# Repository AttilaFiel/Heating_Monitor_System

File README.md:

# HMS – Fűtésfelügyeleti rendszer

### HMS_Master
A rendszer központi egysége, amely a kazánházban található érzékelők adatait gyűjti és feldolgozza. Figyeli a fűtési rendszer hőmérsékleteit, a kazánok működését és a különböző hibajelzéseket. Az adatokat kijelzi, naplózza, valamint Wi-Fi-n keresztül elérhetővé teszi a többi eszköz és a központi felügyeleti rendszer számára. Vizuális és hangjelzésekkel figyelmeztet a rendellenes működésre.

### HMS_Display
A HMS_Master és a HMS_Kids_Thermometer adatait megjelenítő, önállóan működő kijelzőegység, amely a lakótérben helyezhető el. Érintőképernyőjén megjeleníti a fűtési rendszer aktuális állapotát, a hőmérsékleteket, a páratartalmat és a riasztásokat. Hang- és fényjelzésekkel figyelmeztet a fontosabb eseményekre. Wi-Fi-n keresztül kommunikál a többi eszközzel.

### HMS_Kids_Thermometer
Önálló, Wi-Fi-kapcsolattal rendelkező szobai hőmérséklet- és páratartalom-mérő eszköz. Az SHT30 érzékelő segítségével méri a környezeti hőmérsékletet és páratartalmat. A mért adatokat hálózaton keresztül elérhetővé teszi, így a szoba klímája távolról is ellenőrizhető. Elsősorban a gyerekszoba környezeti viszonyainak folyamatos megfigyelésére szolgál.

</br>

# HMS hardverlista

## HMS_Master

### Hardver:
- ESP32 DevKitC-32UE mikrokontroller
- 2× SSD1306 SPI OLED kijelzőmodul
- DS3231 RTC + AT24C32 EEPROM valós idejű óramodul
- MAX6675 K-típusú hőmérséklet-érzékelő modul
- 5× DS18B20 digitális hőmérséklet-érzékelő
- DHT11 hőmérséklet- és páratartalom-érzékelő
- microSD SPI memóriakártya-modul
- 2× MVPDM-1PHS váltakozó feszültség érzékelőmodul
- 3× közös katódos RGB LED
- Aktív hangjelző (buzzer)

### Tápellátás:
- 5 V-os tápbemenet
- Beépített 3,3 V-os feszültségszabályozó

---

## HMS_Display

### Hardver:
- ESP32 DevKitC-32UE mikrokontroller
- MSP2807 2,8"-os TFT SPI érintőképernyő-modul (ILI9341 + XPT2046)
- DS3231 RTC + AT24C32 EEPROM valós idejű óramodul
- SHT30-M hőmérséklet- és páratartalom-érzékelő
- Fényérzékelő (fotóellenállás)
- Közös katódos RGB LED
- 2× aktív hangjelző (buzzer)

### Tápellátás:
- 5 V-os USB-tápbemenet
- Beépített 3,3 V-os feszültségszabályozó

---

## HMS_Kids_Thermometer

### Hardver:
- ESP32-C3-SUPERMINI mikrokontroller
- SHT30 hőmérséklet- és páratartalom-érzékelő

### Tápellátás:
- 5 V-os tápbemenet
- Beépített 3,3 V-os feszültségszabályozó

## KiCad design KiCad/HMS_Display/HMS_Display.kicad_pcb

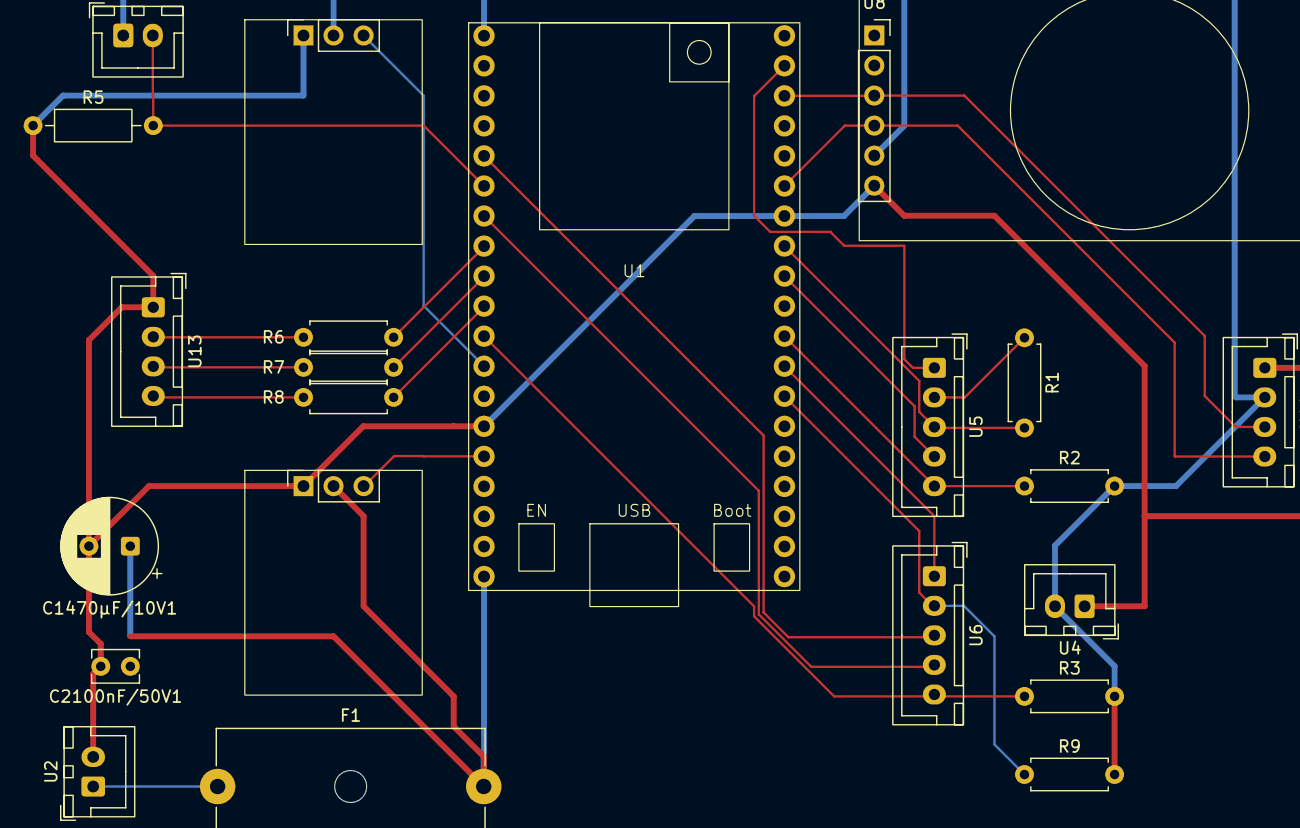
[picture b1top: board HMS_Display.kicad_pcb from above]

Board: 2 copper layers, 22 parts (0 on the bottom side), 25 nets.

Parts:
C1470µF/10V1: 470µF 10V; CP_Radial_D8.0mm_P3.50mm
C2100nF/50V1: 100nF 50V; C_Disc_D3.8mm_W2.6mm_P2.50mm
F1: T1A Fuse; Fuseholder_Cylinder-5x20mm_Schurter_0031_8201_Horizontal_Op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
R1: DNP SOCKET; R_Axial_DIN0207_L6.3mm_D2.5mm_P7.62mm_Horizontal
R2, R3, R9: SOCKET; R_Axial_DIN0207_L6.3mm_D2.5mm_P7.62mm_Horizontal
R5: 10kΩ; R_Axial_DIN0207_L6.3mm_D2.5mm_P10.16mm_Horizontal
R6, R7, R8: 220Ω; R_Axial_DIN0207_L6.3mm_D2.5mm_P7.62mm_Horizontal
U1: ESP32-DEVKITC-32UE; ESP32_DEVKITC_32UE
U2: USB-C_POWER_CONNECTOR; JST_XH_B2B-XH-A_1x02_P2.50mm_Vertical
U4: DISPLAY_POWER_CONNECTOR; JST_XH_B2B-XH-A_1x02_P2.50mm_Vertical
U5: DISPLAY_DATA_CONNECTOR_1; JST_XH_B5B-XH-A_1x05_P2.50mm_Vertical
U6: DISPLAY_DATA_CONNECTOR_2; JST_XH_B5B-XH-A_1x05_P2.50mm_Vertical
U8: DS3231+AT24C32; PinSocket_1x06_P2.54mm_Vertical
U9, U10: KY-012
U11: SHT30_CONNECTOR; JST_XH_B4B-XH-A_1x04_P2.50mm_Vertical
U12: PHOTORESISTOR_CONNECTOR; JST_XH_B2B-XH-A_1x02_P2.50mm_Vertical
U13: LED_CONNECTOR; JST_XH_B4B-XH-A_1x04_P2.50mm_Vertical

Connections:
/01_ESP32/BUZZER_1: U1.12 (GPIO14), U9.3 (SIGNAL)
/01_ESP32/BUZZER_2: U1.15 (GPIO13), U10.3 (SIGNAL)
/01_ESP32/DISPLAY_CS: R2.1, U1.30 (GPIO17), U5.5
/01_ESP32/DISPLAY_DC: U1.31 (GPIO16), U6.1
/01_ESP32/DISPLAY_LED: U1.7 (GPIO32), U6.4
/01_ESP32/DISPLAY_RESET: R9.1, U1.32 (GPIO4), U6.2
/01_ESP32/I2C_SCL: U1.22 (GPIO22), U8.3 (SCL), U11.3
/01_ESP32/I2C_SDA: U1.25 (GPIO21), U8.4 (SDA), U11.4
/01_ESP32/LED_B: R8.1, U1.10 (GPIO26)
/01_ESP32/LED_G: R7.1, U1.9 (GPIO25)
/01_ESP32/LED_R: R6.1, U1.8 (GPIO33)
/01_ESP32/PHOTORESISTOR: R5.2, U1.6 (GPIO35), U12.2
/01_ESP32/PWR_3V3_OUT: R2.2, R3.2, R9.2, U1.1 (3V3), U4.2, U8.5 (VCC), U9.2 (VCC), U11.2, U12.1
/01_ESP32/PWR_5V_IN: C1470µF/10V1.1, C2100nF/50V1.1, F1.2, U1.19 (5V), U10.2 (VCC)
/01_ESP32/PWR_GND: C1470µF/10V1.2, C2100nF/50V1.2, R5.1, U1.14 (GND), U1.20 (GND), U1.26 (GND), U2.2, U4.1, U8.6 (GND), U9.1 (GRN), U10.1 (GRN), U11.1, U13.1
/01_ESP32/SPI_MISO: R1.2, U1.27 (GPIO19), U5.3
/01_ESP32/SPI_MOSI: U1.21 (GPIO23), U5.1
/01_ESP32/SPI_SCK: U1.28 (GPIO18), U5.4
/01_ESP32/T_CS: R3.1, U1.11 (GPIO27), U6.5
/01_ESP32/T_IRQ: U1.5 (GPIO34), U6.3
unnamed: F1.1, U2.1
unnamed: R1.1, U5.2
unnamed: R6.2, U13.2
unnamed: R7.2, U13.3
unnamed: R8.2, U13.4

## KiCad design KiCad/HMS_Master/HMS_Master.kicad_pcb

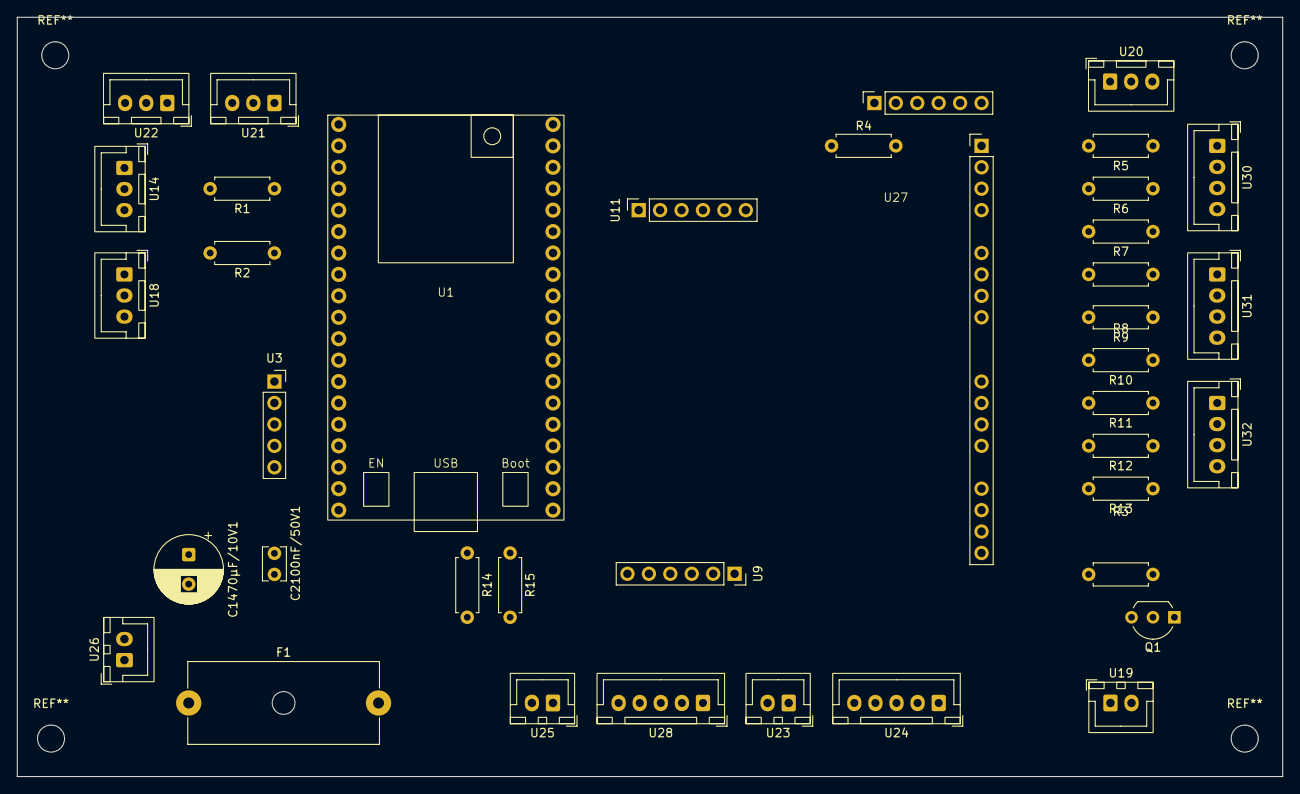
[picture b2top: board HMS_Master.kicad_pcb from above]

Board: 2 copper layers, 150.0 x 90.0 mm, 38 parts (0 on the bottom side), 44 nets.

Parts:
C1470µF/10V1: 470µF 10V; CP_Radial_D8.0mm_P3.50mm
C2100nF/50V1: 100nF 50V; C_Disc_D3.8mm_W2.6mm_P2.50mm
F1: T1A Fuse; Fuseholder_Cylinder-5x20mm_Schurter_0031_8201_Horizontal_Op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
Q1: S8050; TO-92_Inline_Wide
R1: 4,7kΩ; R_Axial_DIN0207_L6.3mm_D2.5mm_P7.62mm_Horizontal
R2: 33Ω; R_Axial_DIN0207_L6.3mm_D2.5mm_P7.62mm_Horizontal
R3: 1kΩ; R_Axial_DIN0207_L6.3mm_D2.5mm_P7.62mm_Horizontal
R4: 10kΩ; R_Axial_DIN0207_L6.3mm_D2.5mm_P7.62mm_Horizontal
R5, R6, R7, R8, R9, R10, R11, R12, R13: 220Ω; R_Axial_DIN0207_L6.3mm_D2.5mm_P7.62mm_Horizontal
R14, R15: 100Ω; R_Axial_DIN0207_L6.3mm_D2.5mm_P7.62mm_Horizontal
U1: ESP32-DEVKITC-32UE; ESP32_DEVKITC_32UE
U3: MAX6675; PinSocket_1x05_P2.54mm_Vertical
U9: DS3231+AT24C32; PinSocket_1x06_P2.54mm_Vertical
U11: MICROSD_SPI_3V3; PinSocket_1x06_P2.54mm_Vertical
U14: PIPE_SENSORS_SOCKET; JST_XH_B3B-XH-A_1x03_P2.50mm_Vertical
U18: WOOD_BOILER_SENSOR_SOCKET; JST_XH_B3B-XH-A_1x03_P2.50mm_Vertical
U19: BUZZER_SOCKET; JST_XH_B2B-XH-A_1x02_P2.50mm_Vertical
U20: BOILER_ROOM_SENSOR_SOCKET; JST_XH_B3B-XH-A_1x03_P2.50mm_Vertical
U21: GAS_AC_PRESENT_SOCKET; JST_XH_B3B-XH-A_1x03_P2.50mm_Vertical
U22: WOOD_AC_PRESENT_SOCKET; JST_XH_B3B-XH-A_1x03_P2.50mm_Vertical
U23: DISPLAY1_POWER_SOCKET; JST_XH_B2B-XH-A_1x02_P2.50mm_Vertical
U24: DISPLAY1_DATA_SOCKET; JST_XH_B5B-XH-A_1x05_P2.50mm_Vertical
U25: DISPLAY2_POWER_SOCKET; JST_XH_B2B-XH-A_1x02_P2.50mm_Vertical
U26: USB_Micro-B_Socket; JST_XH_B2B-XH-A_1x02_P2.50mm_Vertical
U27: SERVO16-1A-SLD
U28: DISPLAY2_DATA_SOCKET; JST_XH_B5B-XH-A_1x05_P2.50mm_Vertical
U30: LED_GAS_SOCKET; JST_XH_B4B-XH-A_1x04_P2.50mm_Vertical
U31: LED_WOOD_SOCKET; JST_XH_B4B-XH-A_1x04_P2.50mm_Vertical
U32: LED_STATUS_SOCKET; JST_XH_B4B-XH-A_1x04_P2.50mm_Vertical

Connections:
/01_ESP32/BOILER_ROOM_TEMPERATURE: U1.10 (GPIO26), U20.2
/01_ESP32/BUZZER: R3.1, U1.9 (GPIO25)
/01_ESP32/CHIMNEY_TEMPERATURE_CS: U1.12 (GPIO14), U3.4 (CS)
/01_ESP32/DISPLAY1_CS: R14.1, U1.29 (GPIO5)
/01_ESP32/DISPLAY2_CS: R15.1, U1.32 (GPIO4)
/01_ESP32/DISPLAY_DC: U1.30 (GPIO17), U24.4, U28.4
/01_ESP32/DISPLAY_RESET: U1.31 (GPIO16), U24.3, U28.3
/01_ESP32/GAS_AC_PRESENT: U1.7 (GPIO32), U21.2
/01_ESP32/I2C_SCL: U1.22 (GPIO22), U9.3 (SCL), U27.3 (SCL)
/01_ESP32/I2C_SDA: U1.25 (GPIO21), U9.4 (SDA), U27.4 (SDA)
/01_ESP32/MICROSD_CS: U1.15 (GPIO13), U11.2 (CS)
/01_ESP32/PWR_3V3_OUT: R1.1, U1.1 (3V3), U3.2 (VCC), U9.5 (VCC), U11.1 (3v3), U14.1, U18.1, U20.1, U21.1, U22.1, U23.2, U25.2, U27.5 (VCC)
/01_ESP32/PWR_5V_IN: C1470µF/10V1.1, C2100nF/50V1.1, F1.2, U1.19 (5V), U19.1
/01_ESP32/PWR_GND: C1470µF/10V1.2, C2100nF/50V1.2, Q1.1 (E), R4.1, U1.14 (GND), U1.20 (GND), U1.26 (GND), U3.1 (GND), U9.6 (GND), U11.6 (GND), U14.3, U18.3, U20.3, U21.3, U22.3, U23.1, U25.1, U26.2, U27.1 (GND), U30.2, U31.2, U32.2
/01_ESP32/SPI_MISO: U1.27 (GPIO19), U3.5 (SO), U11.5 (MISO)
/01_ESP32/SPI_MOSI: U1.21 (GPIO23), U11.3 (MOSI), U24.2, U28.2
/01_ESP32/SPI_SCK: U1.28 (GPIO18), U3.3 (SCK), U11.4 (CLK), U24.1, U28.1
/01_ESP32/TEMPERATURE_SENSOR_BUS: R2.1, U1.11 (GPIO27)
/01_ESP32/WOOD_AC_PRESENT: U1.8 (GPIO33), U22.2
unnamed: F1.1, U26.1
unnamed: Q1.2 (B), R3.2
unnamed: Q1.3 (C), U19.2
unnamed: R1.2, R2.2, U14.2, U18.2
unnamed: R5.1, U30.1
unnamed: R6.1, U30.3
unnamed: R7.1, U30.4
unnamed: R8.1, U31.1
unnamed: R9.1, U31.3
unnamed: R10.1, U31.4
unnamed: R11.1, U32.1
unnamed: R12.1, U32.3
unnamed: R13.1, U32.4
unnamed: R14.2, U24.5
unnamed: R15.2, U28.5
unnamed: R4.2, U27.2 (OE)
unnamed: R5.2, U27.7 (PWM0)
unnamed: R6.2, U27.8 (PWM1)
unnamed: R7.2, U27.9 (PWM2)
unnamed: R8.2, U27.10 (PWM3)
unnamed: R9.2, U27.11 (PWM4)
unnamed: R10.2, U27.12 (PWM5)
unnamed: R11.2, U27.13 (PWM6)
unnamed: R12.2, U27.14 (PWM7)
unnamed: R13.2, U27.15 (PWM8)

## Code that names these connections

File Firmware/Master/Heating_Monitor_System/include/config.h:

#include "secrets.h"

#pragma once

// --------------------------------
// Hálózati beállítások
// --------------------------------

// Wi-fi csatlakozási adatok
// secrets.h fájlban definiálva
//#define WIFI_SSID "YOUR_WIFI_SSID"
//#define WIFI_PASSWORD "YOUR_WIFI_PASSWORD"

// Wi-Fi terminál
#define TERMINAL_PORT 36987

// OTA
#define OTA_HOSTNAME "HMS-ESP32"

// --------------------------------
// GPIO pin definíciók
// --------------------------------

// I2C
#define I2C_SDA 21
#define I2C_SCL 22

// PCA9685
#define PCA9685_ADDRESS 0x40
#define PCA9685_PWM_FREQ 1000

// MicroSD / SPI
#define MICROSD_CS 13

#define SPI_SCK 18
#define SPI_MISO 19
#define SPI_MOSI 23

// MAX6675
#define CHIMNEY_TEMPERATURE_CS 14

// DHT11
#define BOILER_ROOM_TEMPERATURE 26

// MVPDM-1PHS AC JELENLÉT ÉRZÉKELŐK
#define GAS_AC_PRESENT 32
#define WOOD_AC_PRESENT 33

// Buzzer
#define BUZZER 25
#define BUZZER_ENABLED false

// DS18B20 hőmérséklet szenzorok
// DS18B20 OneWire
#define TEMPERATURE_SENSOR_BUS 27

// DS18B20 Szenzorok egyedi címei
#define GAS_FLOW_SENSOR       "2842FF9590250667"
#define GAS_RETURN_SENSOR     "2850D68990250673"

#define WOOD_FLOW_SENSOR      "28CE7739902506BE"
#define WOOD_RETURN_SENSOR    "2827C42D9125069D"

#define WOOD_BOILER_SENSOR    "28711D9E912506B5"


// SSD1306 KIJEZOK
// Kijelzők közös vezérlő jelei
#define DISPLAY_RESET 16
#define DISPLAY_DC 17

// Kijelzők Chip Select jelei
#define DISPLAY1_CS 5
#define DISPLAY2_CS 4

// RGB LED csatornák
#define RGB_LED_GAS 1   //Gáz
#define RGB_LED_WOOD 0  //Fa
#define RGB_LED_ESP32 2 //ESP32 státusz

// --------------------------------
// Hőmérséklet határértékek
// --------------------------------
#define FIRE_TEMPERATURE_THRESHOLD       80.0

#define WOOD_FLOW_HEATING_THRESHOLD      28.0
#define WOOD_FLOW_COOLING_THRESHOLD      22.0

#define WOOD_BOILER_OPTIMAL_TEMPERATURE  60.0
#define WOOD_BOILER_WARNING_TEMPERATURE  70.0
#define WOOD_BOILER_ALARM_TEMPERATURE    80.0

#define STARTUP_TIMEOUT                 900000UL   // 15 perc
#define WOOD_AC_SWITCH_TIMEOUT          120000UL   // 2 perc


// =========================================================
// TESZT BEÁLLÍTÁSOK
// =========================================================

// Riasztási prioritás teszt
#define ALARM_PRIORITY_TEST_ENABLED false
#define ALARM_TEST_STEP_TIME 30000UL

// AC jelenlét teszt
#define AC_PRESENCE_TEST_ENABLED false
#define AC_TEST_STEP_TIME 30000UL

// Kazán túlmelegedés teszt
#define BOILER_OVERHEAT_TEST_ENABLED false
#define BOILER_TEST_STEP_TIME 30000UL

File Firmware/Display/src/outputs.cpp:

#include "outputs.h"

#include <Arduino.h>

#include "config.h"


// ============================================================
// Segédfüggvények
// ============================================================

// Százalék átalakítása 0–255 közötti PWM értékre
static uint8_t duty(uint8_t p) {
    return (uint16_t)p * 255 / 100;
}


// RGB LED vezérlése
static void rgb(bool r, bool g, bool b, uint8_t p) {
    ledcWrite(1, r ? duty(p) : 0);
    ledcWrite(2, g ? duty(p) : 0);
    ledcWrite(3, b ? duty(p) : 0);
}


// ============================================================
// Globális változók
// ============================================================

static uint32_t alarmStart = 0;


// ============================================================
// Kimenetek inicializálása
// ============================================================

void outputsBegin() {
    // Hangjelzők konfigurálása
    pinMode(PIN_BUZZER_1, OUTPUT);
    pinMode(PIN_BUZZER_2, OUTPUT);

    digitalWrite(PIN_BUZZER_1, LOW);
    digitalWrite(PIN_BUZZER_2, LOW);


    // Piros RGB csatorna
    ledcSetup(1, 5000, 8);
    ledcAttachPin(PIN_LED_R, 1);


    // Zöld RGB csatorna
    ledcSetup(2, 5000, 8);
    ledcAttachPin(PIN_LED_G, 2);


    // Kék RGB csatorna
    ledcSetup(3, 5000, 8);
    ledcAttachPin(PIN_LED_B, 3);
}


// ============================================================
// Kimenetek frissítése
// ============================================================

void outputsUpdate(
    const String& s,
    const String& branch,
    const String& a,
    bool dark
) {
    // RGB LED fényerejének kiválasztása
    uint8_t p = dark
        ? RGB_DARK_PERCENT
        : RGB_BRIGHTNESS_PERCENT;

    if (a == "ALARM_WARNING" || a == "ALARM_CRITICAL") {
        p = RGB_ALARM_PERCENT;
    }


    // --------------------------------------------------------
    // Kritikus riasztás
    // --------------------------------------------------------

    if (a == "ALARM_CRITICAL") {
        rgb(true, false, false, p);

        digitalWrite(PIN_BUZZER_1, LOW);

        digitalWrite(
            PIN_BUZZER_2,
            (millis() % 1000) < 500 ? HIGH : LOW
        );

        return;
    }


    // --------------------------------------------------------
    // Figyelmeztető riasztás
    // --------------------------------------------------------

    if (a == "ALARM_WARNING") {
        rgb(true, true, false, p);

        digitalWrite(PIN_BUZZER_2, LOW);

        digitalWrite(
            PIN_BUZZER_1,
            (millis() % 1250) < 250 ? HIGH : LOW
        );

        return;
    }


    // --------------------------------------------------------
    // Nincs aktív riasztás
    // --------------------------------------------------------

    digitalWrite(PIN_BUZZER_1, LOW);
    digitalWrite(PIN_BUZZER_2, LOW);


    // --------------------------------------------------------
    // Üzemi állapot szerinti RGB LED
    // --------------------------------------------------------

    if (
        s == "SYSTEM_STARTUP" ||
        s == "SYSTEM_FIRE_WITHOUT_CIRCULATOR"
    ) {
        rgb(true, false, true, p);
    }
    else if (
        branch == "HEATING_GAS" ||
        s == "SYSTEM_GAS"
    ) {
        rgb(false, false, true, p);
    }
    else if (
        branch == "HEATING_WOOD" ||
        s == "SYSTEM_WOOD"
    ) {
        rgb(false, true, false, p);
    }
    else {
        rgb(false, false, false, p);
    }
}
